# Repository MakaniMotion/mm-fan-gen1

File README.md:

# MakaniMotion MM-Fan GEN 1

A modular DIY fan platform.

## Table of Contents

- [Overview](#overview)
- [Motivation](#motivation)
- [Modules](#modules)
  - [MM-BASE](#mm-base)
  - [MM-AIR](#mm-air)
  - [MM-TRI](#mm-tri)
- [System Parts](#system-parts)
- [Build Configurations](#build-configurations)
  - [Table Version](#table-version)
  - [Stand Version](#stand-version)
- [Project Status](#project-status)
- [License / Usage](#license--usage)

## Overview

MakaniMotion MM-Fan GEN 1 is a modular DIY fan platform built around interchangeable modules.

The system can be assembled in different configurations and combines PC fan hardware, 3D-printed mechanical parts and a simple control interface.

## Motivation

The goal of this project is to develop a fan system that is quiet, modular, energy-efficient and visually aesthetic.

The design is based on high-performance PC / gaming fans. These fans are developed in a highly competitive market and are therefore typically optimized for low noise, low power consumption and high airflow.

The main challenge of MakaniMotion MM-Fan GEN 1 is to adapt these properties to the use case of a room fan. Instead of only moving air through a PC case, radiator or filter, the system is designed to create a more focused and usable airflow for indoor use.

## Modules

MakaniMotion MM-Fan GEN 1 is built around three main modules. Each module has a dedicated function and can be combined with the other modules depending on the desired build configuration.

### MM-BASE

**MM-BASE** is the base and control module of the system.

It provides the main electrical control interface, power distribution and user interface for the fan setup. The GEN 1 main PCBA uses an Arduino Nano to keep the project easy to reproduce.

MM-BASE is intended to be powered from a suitable 5 V USB power bank. The enclosure is designed to fit smaller power banks inside the module, allowing the system to be used as a battery-powered device without using a custom battery pack.

In the current GEN 1 prototype, MM-BASE may not work directly with all USB chargers. A power source with an active/default 5 V output is required.

| Item | Description |
|---|---|
| Module name | MM-BASE |
| Main PCBA | mm-main-pcba-gen1-reva |
| Controller | Arduino Nano |
| Power input | 5 V |
| Recommended power source | Suitable USB power bank |
| Power source requirement | Active/default 5 V output |
| Power bank integration | Enclosure space for smaller power banks |
| Power stage | 10 W DC/DC converter |
| Supported MM-AIR modules | Up to 5 MM-AIR modules in the current setup |
| HMI | One push button for PWM level selection |
| Status indication | Four RGB LEDs indicate the selected PWM level using different colors |
| Design goal | Easy to build, easy to understand and suitable for DIY reproduction |

### MM-AIR

**MM-AIR** is the fan / airflow module of the system.

It uses a Noctua NF-A12x25 PWM 120 mm fan, selected for its low noise level, low power consumption and high airflow performance.

The fan is mounted to a 3D-printed shroud that reduces the outlet cross-section. This helps increase air velocity and creates a more focused airflow for use as a room fan.

An interface PCB is mounted on the side of the module. The **mm-interface-pcba-gen1-reva** connects MM-AIR to the daisy-chain system and provides two RJ45 sockets and one PC fan header.

| Item | Description |
|---|---|
| Module name | MM-AIR |
| Fan | Noctua NF-A12x25 PWM |
| Fan size | 120 mm |
| Fan control | PWM |
| Interface PCBA | mm-interface-pcba-gen1-reva |
| System connectors | 2 × RJ45 sockets for daisy-chain connection |
| Fan connector | 1 × PC fan header |
| Mechanical design | 3D-printed shroud |
| Airflow concept | Reduced outlet cross-section to increase air velocity |
| Design goal | Quiet operation with focused, usable airflow |

### MM-TRI

**MM-TRI** is the tripod module for the free-standing build configuration.

It provides a simple and stable three-leg support structure for the system.

The three-leg design avoids mechanical overconstraint and helps the fan stand securely on uneven surfaces.

The module is intentionally kept simple and minimal while still maintaining an elegant appearance. In the current version, MM-TRI is attached to MM-BASE using three screws, making it easy to switch between the table version and the free-standing configuration.

| Item | Description |
|---|---|
| Module name | MM-TRI |
| Module type | Tripod module |
| Mechanical concept | Three-leg support structure to avoid mechanical overconstraint |
| Mounting interface | Attached to MM-BASE using a single screw |
| Required for | Stand version |
| Design goal | Simple, stable and elegant free-standing support |

## System Parts

The system also includes physical parts that belong to the overall GEN 1 system but are not assigned to a single module.

- **MM-CONNECT** – mechanical connection element
- **Connection Cables** – The connection cables are based on RJ45, but they are not used for Ethernet networking. They are repurposed as system connection cables for power and signals between modules.

## Build Configurations

MakaniMotion MM-Fan GEN 1 can typically be assembled in two main configurations:

### Table Version

The table version is designed to be placed on a desk or similar surface.

In this configuration, the **MM-TRI** tripod module is not required.

Because the modules are connected by cables, the physical layout can be adapted to different use cases and desk setups.

### Stand Version

The stand version is designed as a free-standing fan setup.

In this configuration, the **MM-TRI** tripod module is required.

## Project Status

Prototype / work in progress.

This repository contains the first product generation:

```text
MakaniMotion MM-Fan GEN 1
```

Module revisions within this generation are tracked separately, for example:

```text
MM-Base GEN 1 Rev A
MM-Air GEN 1 Rev A
MM-TRI GEN 1 Rev A
```

This project is a DIY development project and is not a certified consumer product.

No CE declaration, conformity assessment or safety certification.

Anyone building hardware based on this project does so at their own risk and is responsible for safe assembly and operation.

## License / Usage

This project is source-available for private and non-commercial use only.

Private individuals may view, download, build and modify the project files for personal use.

Non-commercial sharing or uploading of modified project files is allowed if MakaniMotion is clearly credited as the original source and this license remains included.

Commercial use is not permitted. This includes use by companies, commercial organizations, paid services, commercial product development, manufacturing for commercial purposes, or distributing physical devices, kits, parts or assemblies based on this project.

For details, see [`LICENSE.md`](LICENSE.md).

© MakaniMotion. All rights reserved unless otherwise stated.

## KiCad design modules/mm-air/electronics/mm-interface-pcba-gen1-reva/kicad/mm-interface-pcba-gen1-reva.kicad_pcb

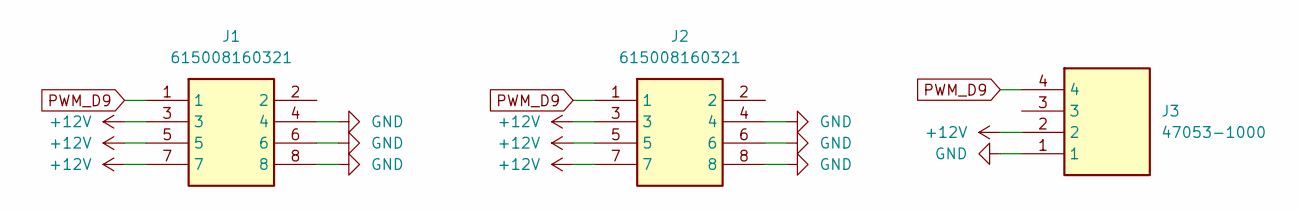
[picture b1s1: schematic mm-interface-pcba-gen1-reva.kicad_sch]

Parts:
J1, J2: 615008160321; Mouser Part Number 710-615008160321
J3: 47053-1000; 470531000; Mouser Part Number 538-47053-1000

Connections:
+12V: J1.3, J1.5, J1.7, J2.3, J2.5, J2.7, J3.2
GND: J1.4, J1.6, J1.8, J2.4, J2.6, J2.8, J3.1
PWM_D9: J1.1, J2.1, J3.4

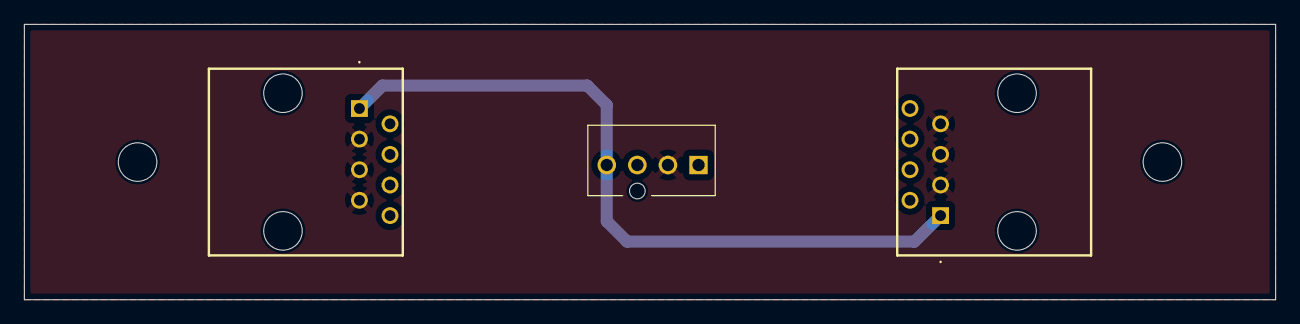
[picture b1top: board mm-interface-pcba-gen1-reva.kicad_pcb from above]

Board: 2 copper layers, 103.9 x 22.9 mm, 3 parts (0 on the bottom side), 3 nets.

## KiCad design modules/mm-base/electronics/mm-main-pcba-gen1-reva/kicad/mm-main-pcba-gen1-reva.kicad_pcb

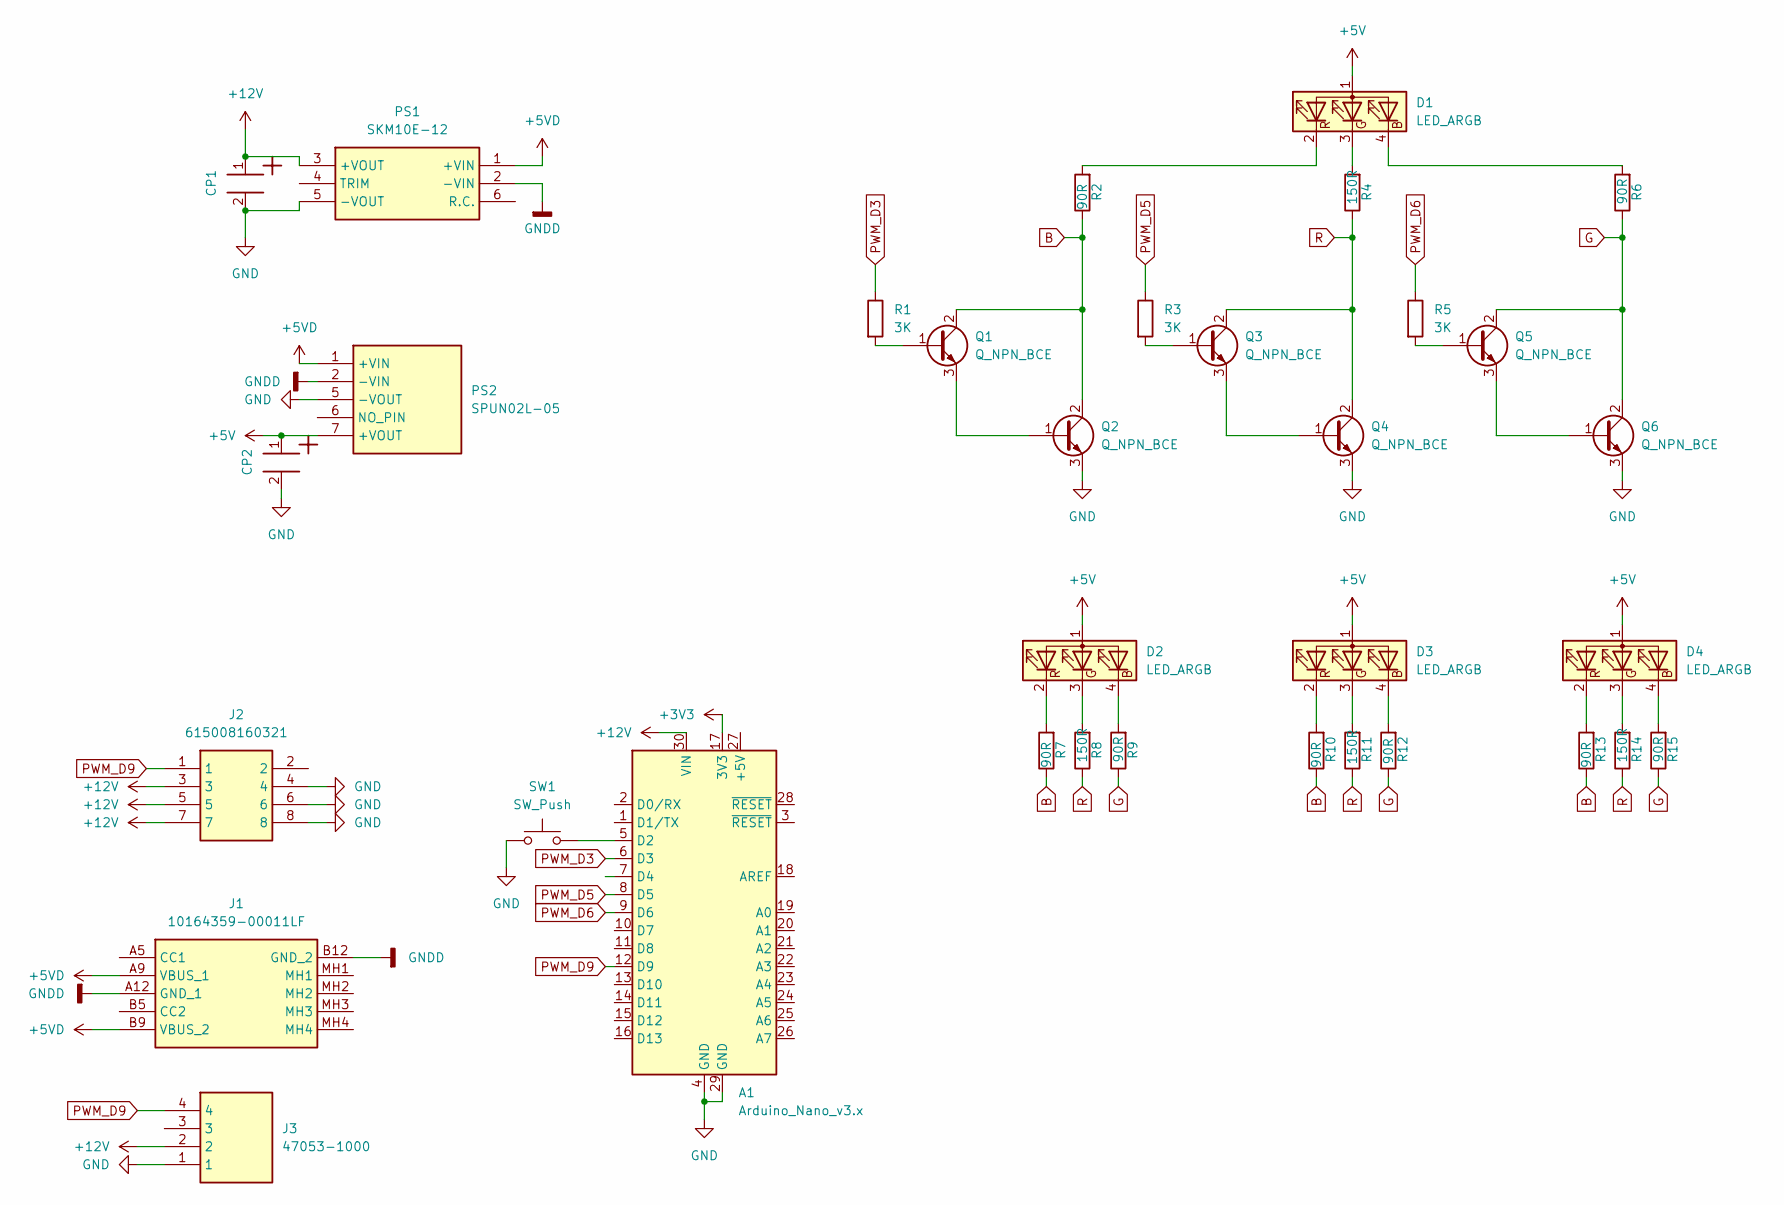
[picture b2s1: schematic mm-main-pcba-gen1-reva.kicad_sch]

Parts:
A1: Arduino_Nano_v3.x; Arduino_Nano
CP1, CP2: P2.5D6.3L11_860010573007_Modified; CP_Wurth_WCAP-ATG8-P2.5D6.3L11; Part Number 860010573007
D1, D2, D3, D4: LED_ARGB; 150141M173100
J1: 10164359-00011LF; 1016435900011LF_handsoldered; Mouser Part Number 649-10164359-00011LF
J2: 615008160321; Mouser Part Number 710-615008160321
J3: 47053-1000; 470531000; Mouser Part Number 538-47053-1000
PS1: SKM10E-12; SKM10B05; Mouser Part Number 709-SKM10E-12
PS2: SPUN02L-05; SPUN02L05; Mouser Part Number 709-SPUN02L-05
Q1, Q2, Q3, Q4, Q5, Q6: Q_NPN_BCE; SOT-23-3
R1, R3, R5: 3K; R_1206_3216Metric_Pad1.30x1.75mm_HandSolder
R2, R6, R7, R9, R10, R12, R13, R15: 90R; R_1206_3216Metric_Pad1.30x1.75mm_HandSolder
R4, R8, R11, R14: 150R; R_1206_3216Metric_Pad1.30x1.75mm_HandSolder
SW1: SW_Push; SW_PUSH_6mm_H13mm

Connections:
+3V3: A1.17 (3V3)
+5V: CP2.1, D1.1 (A), D2.1 (A), D3.1 (A), D4.1 (A), PS2.7 (+VOUT)
+5VD: J1.A9 (VBUS_1), J1.B9 (VBUS_2), PS1.1 (+VIN), PS2.1 (+VIN)
+12V: A1.30 (VIN), CP1.1, J2.3, J2.5, J2.7, J3.2, PS1.3 (+VOUT)
B: Q1.2 (C), Q2.2 (C), R2.1, R7.1, R10.1, R13.1
G: Q5.2 (C), Q6.2 (C), R6.1, R9.1, R12.1, R15.1
GND: A1.4 (GND), A1.29 (GND), CP1.2, CP2.2, J2.4, J2.6, J2.8, J3.1, PS1.5 (-VOUT), PS2.5 (-VOUT), Q2.3 (E), Q4.3 (E), Q6.3 (E), SW1.1
GNDD: J1.A12 (GND_1), J1.B12 (GND_2), PS1.2 (-VIN), PS2.2 (-VIN)
unnamed: A1.5 (D2), SW1.2
unnamed: D1.4 (BK), R6.2
unnamed: D1.3 (GK), R4.2
unnamed: D1.2 (RK), R2.2
unnamed: D2.4 (BK), R9.2
unnamed: D2.3 (GK), R8.2
unnamed: D2.2 (RK), R7.2
unnamed: D3.4 (BK), R12.2
unnamed: D3.3 (GK), R11.2
unnamed: D3.2 (RK), R10.2
unnamed: D4.4 (BK), R15.2
unnamed: D4.3 (GK), R14.2
unnamed: D4.2 (RK), R13.2
unnamed: Q1.1 (B), R1.2
unnamed: Q1.3 (E), Q2.1 (B)
unnamed: Q3.1 (B), R3.2
unnamed: Q3.3 (E), Q4.1 (B)
unnamed: Q5.1 (B), R5.2
unnamed: Q5.3 (E), Q6.1 (B)
PWM_D3: A1.6 (D3), R1.1
PWM_D5: A1.8 (D5), R3.1
PWM_D6: A1.9 (D6), R5.1
PWM_D9: A1.12 (D9), J2.1, J3.4
R: Q3.2 (C), Q4.2 (C), R4.1, R8.1, R11.1, R14.1

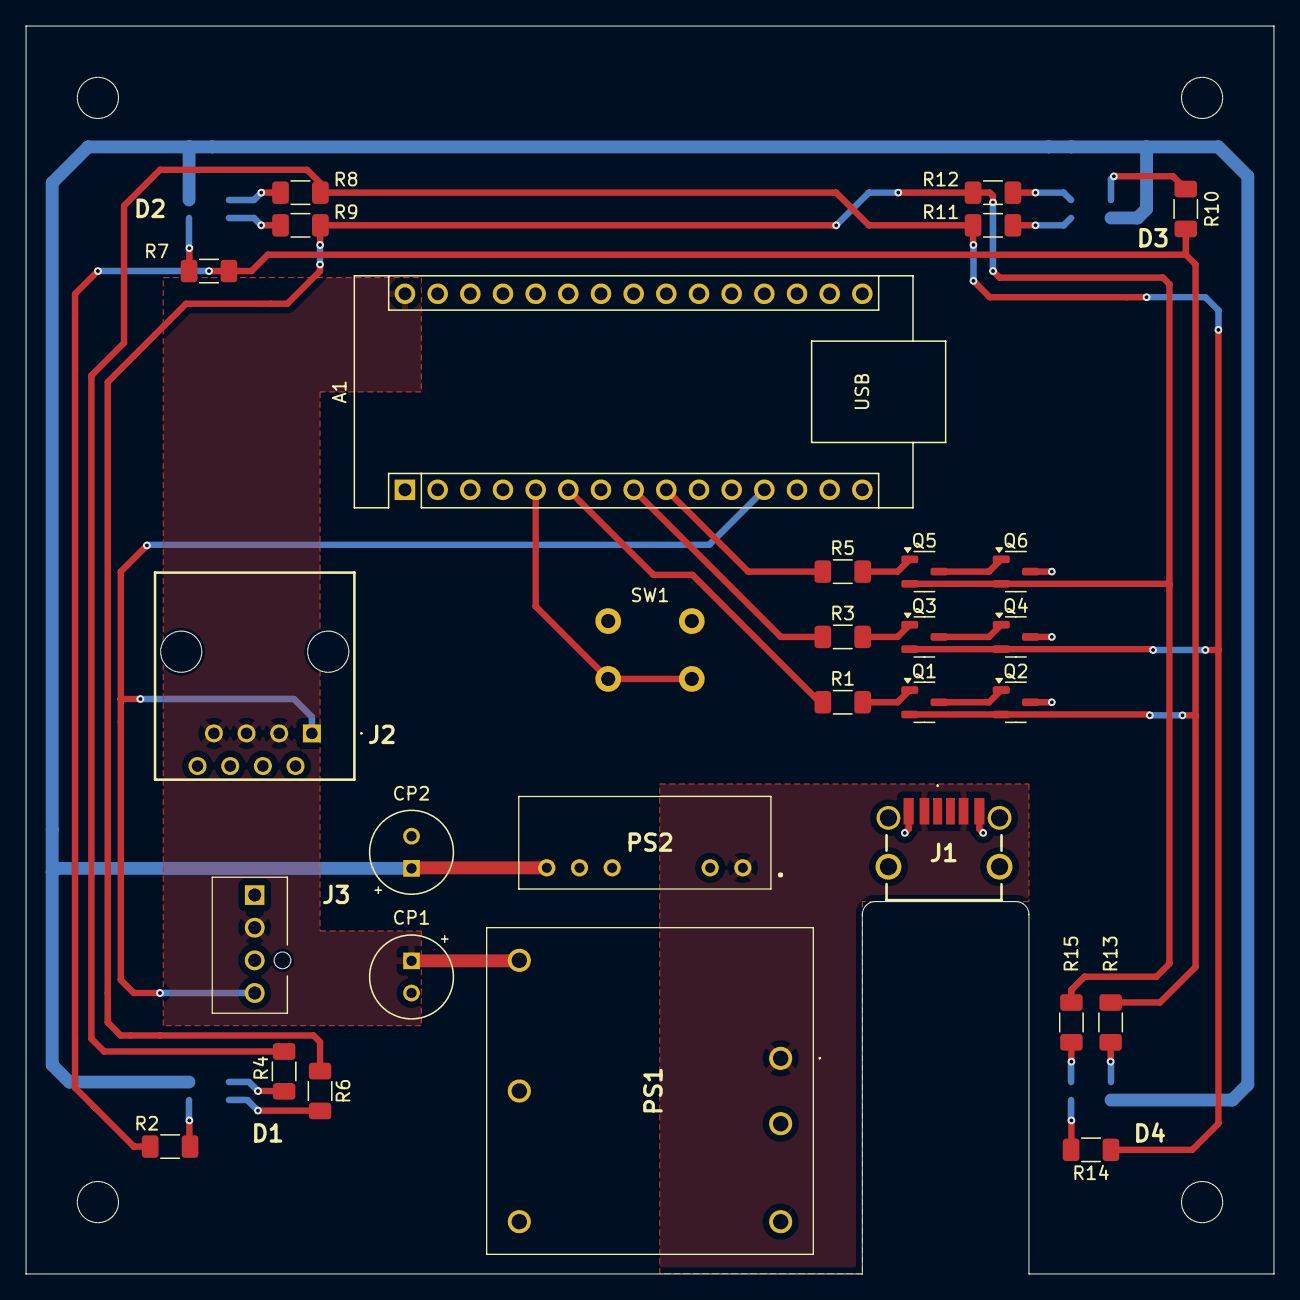
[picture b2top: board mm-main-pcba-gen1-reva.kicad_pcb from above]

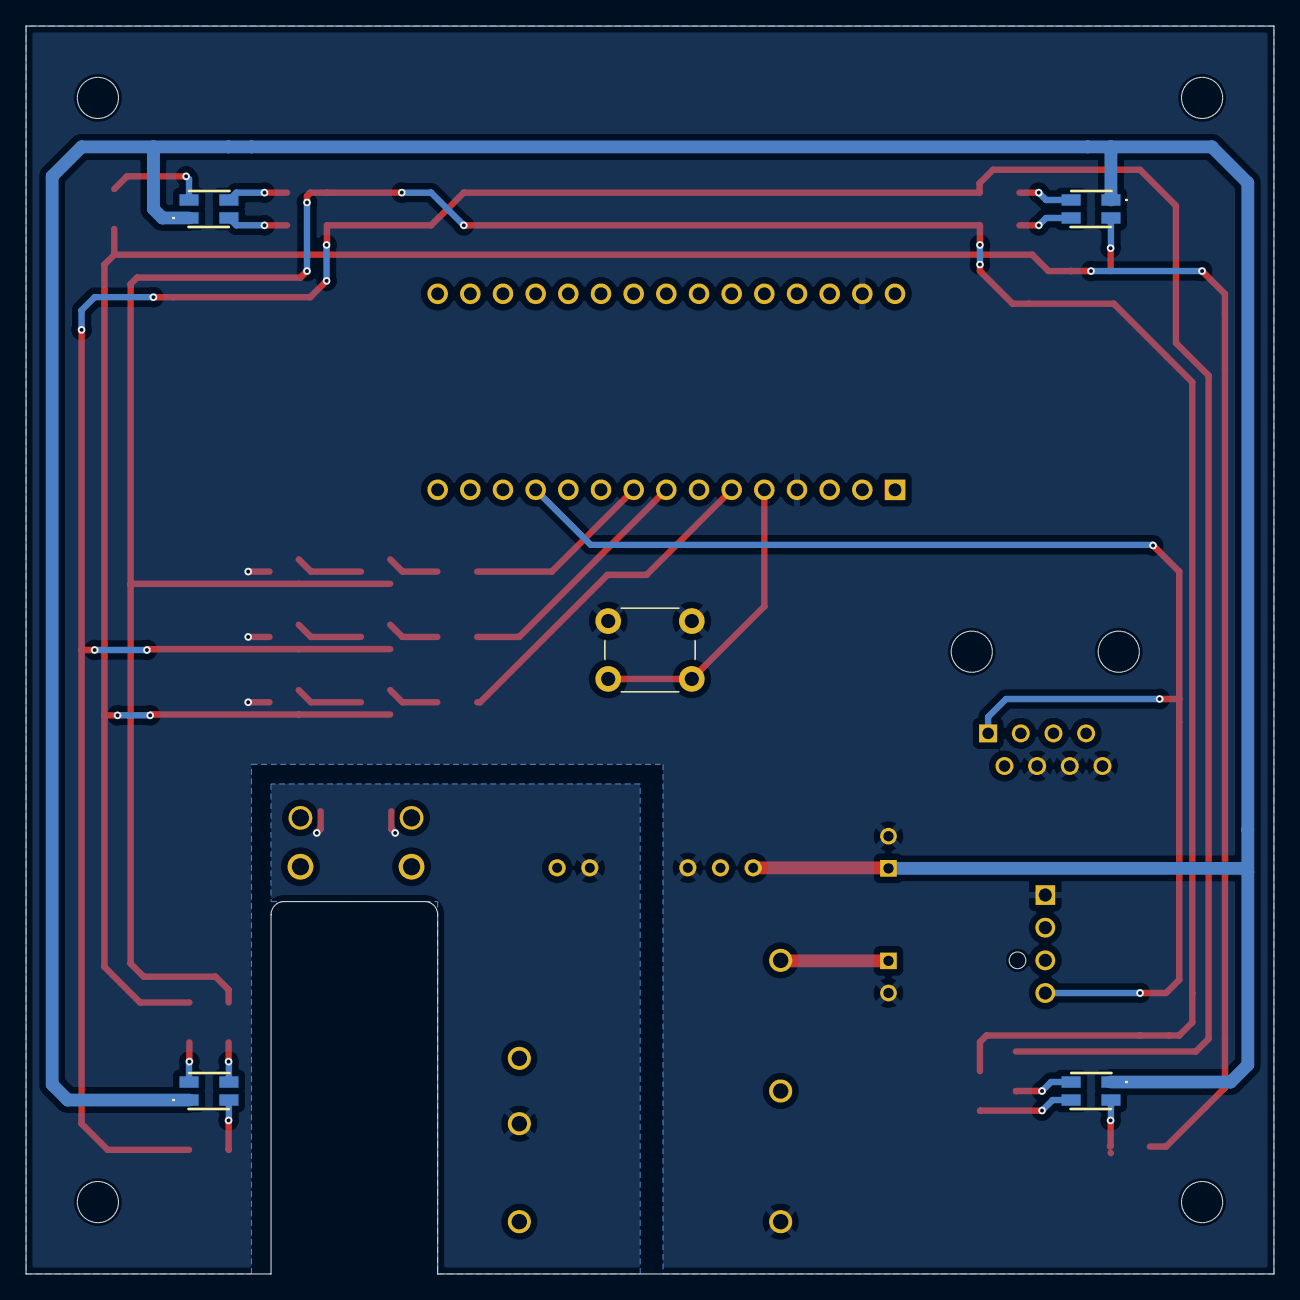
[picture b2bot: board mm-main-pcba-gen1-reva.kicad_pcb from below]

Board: 2 copper layers, 97.0 x 97.0 mm, 34 parts (5 on the bottom side), 31 nets.
